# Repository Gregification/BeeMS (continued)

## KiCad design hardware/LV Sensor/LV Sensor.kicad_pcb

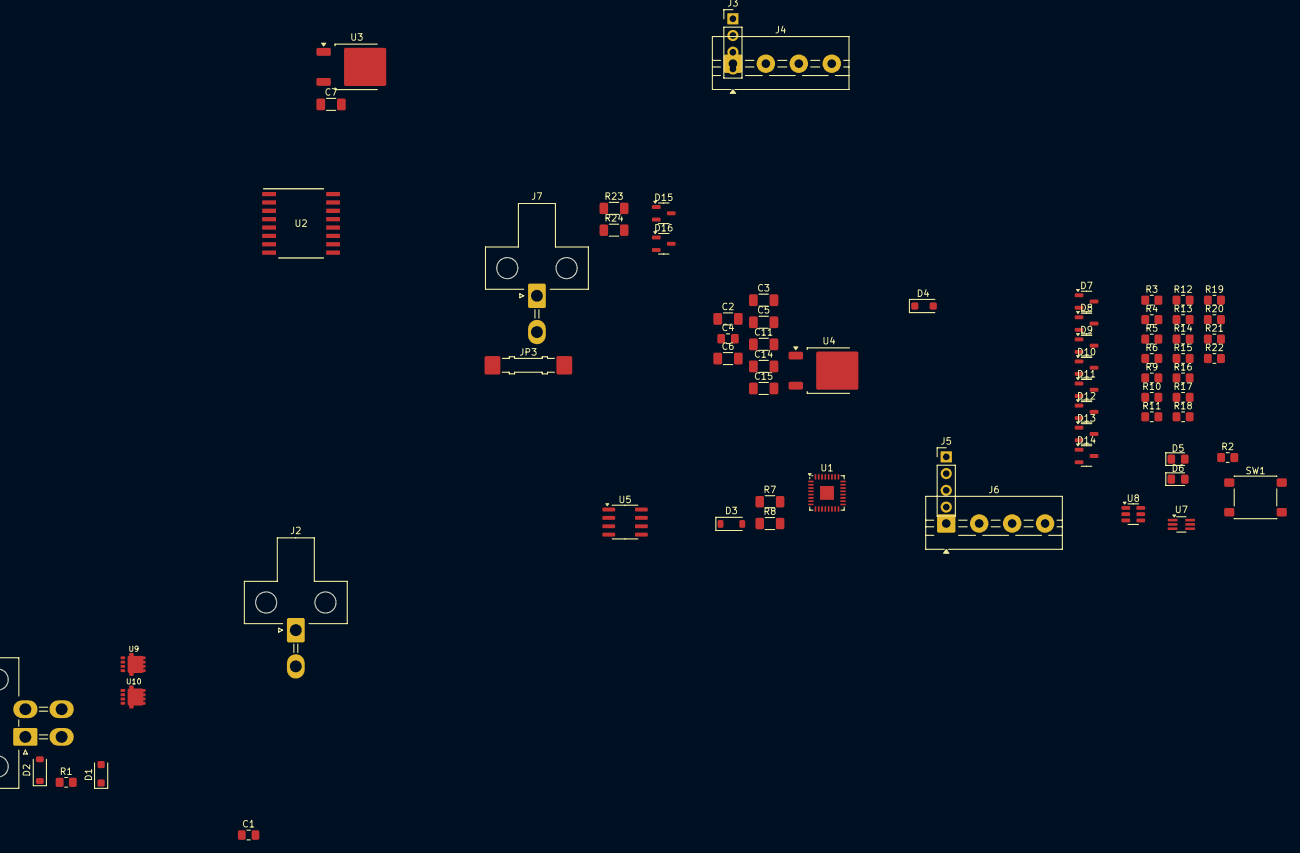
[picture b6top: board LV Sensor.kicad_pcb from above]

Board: 2 copper layers, 68 parts (0 on the bottom side), 42 nets, no tracks yet.

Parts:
C1, C4: 470n; C_0805_2012Metric_Pad1.18x1.45mm_HandSolder
C2, C6, C7, C14: 10u; C_1206_3216Metric_Pad1.33x1.80mm_HandSolder
C3, C15: 100n; C_1206_3216Metric_Pad1.33x1.80mm_HandSolder
C5, C11: 220n; C_1206_3216Metric_Pad1.33x1.80mm_HandSolder
D1, D4: 18V; D_SOD-123F
D2, D3: D_SOD-123
D5: GREEN; D_0805_2012Metric_Pad1.15x1.40mm_HandSolder
D6: RED; D_0805_2012Metric_Pad1.15x1.40mm_HandSolder
D7, D8, D9, D10, D11, D12, D13, D14, D15, D16: BAT54S; SOT-23-3
J1: Conn_01x04_Pin; Molex_Mini-Fit_Jr_5569-04A1_2x02_P4.20mm_Horizontal
J2, J7: Conn_01x02_Pin; Molex_Mini-Fit_Jr_5569-02A1_2x01_P4.20mm_Horizontal
J3, J5: TH; PinHeader_1x04_P2.54mm_Vertical
J4, J6: SCREW; TerminalBlock_MaiXu_MX126-5.0-04P_1x04_P5.00mm
JP3: Jumper_2_Open; Jumper_Harwin_S1621_P10.9mm
R1, R2: 200k; R_0805_2012Metric_Pad1.20x1.40mm_HandSolder
R3, R4: 220; R_0805_2012Metric_Pad1.20x1.40mm_HandSolder
R5, R6, R9, R10, R11, R12, R13, R14, R15, R16, R17, R18, R19, R20, R21, R22: 100k; R_0805_2012Metric_Pad1.20x1.40mm_HandSolder
R7: 49.9k; R_1206_3216Metric_Pad1.30x1.75mm_HandSolder
R8: 100k; R_1206_3216Metric_Pad1.30x1.75mm_HandSolder
R23, R24: 4.99k; R_1206_3216Metric_Pad1.30x1.75mm_HandSolder
SW1: SW_Push; SW_SPST_PTS645Sx43SMTR92
U1: MSPM0G3507 RHB32; Texas_RHB0032M_VQFN-32-1EP_5x5mm_P0.5mm_EP2.1x2.1mm
U2: ISO1042BDW; DW0016B_M
U3, U4: KA78M05_TO252; TO-252-2
U5: L78L33_SO8; SOIC-8_3.9x4.9mm_P1.27mm
U7: HBDM60V600X; SOT-363_SC-70-6_Handsoldering
U8: MCP3421A0T-ECH; SOT-23-6
U9, U10: DXTN80100CFGQ; PowerDI3333-8_SWP

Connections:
+3V3: C2.1, C14.1, C15.1, D7.2 (K), D8.2 (K), D9.2 (K), D10.2 (K), D11.2 (K), D12.2 (K), D13.2 (K), D14.2 (K), R3.2, R4.2, R7.1, R23.1, R24.2, U1.4 (VDD), U5.1 (OUT), U8.5 (V_{DD})
+BATT: D3.2 (A), J2.1
-BATT: C2.2, C3.2, C4.2, C5.2, C6.2, C11.2, C14.2, C15.2, D4.2 (A), D5.1 (K), D6.1 (K), D7.1 (A), D8.1 (A), D9.1 (A), D10.1 (A), D11.1 (A), D12.1 (A), D13.1 (A), D14.1 (A), J2.2, J7.1, JP3.2 (B), R8.1, R11.1, R12.1, R13.1, R14.1, R16.1, R18.1, R20.1, R22.1, SW1.2, U1.5 (VSS), U1.33 (CENTER_PAD), U2.2 (GND1), U2.8 (GND1), U4.2 (GND), U5.2 (GND), U5.3 (GND), U5.6 (GND), U5.7 (GND)
/ADC0_0: D11.3 (COM), R5.2, R11.2, U1.31 (PA27_A0_0_CAN_RX)
/ADC0_1: D12.3 (COM), R6.2, R12.2, U1.30 (PA26_A0_1_CAN_TX)
/ADC0_2: D13.3 (COM), R9.2, R13.2, U1.29 (PA25_A0_2)
/ADC0_3: D14.3 (COM), R10.2, R14.2, U1.28 (PA24_A0_3)
/ADC1_0: D9.3 (COM), R15.2, R16.2, U1.19 (PA15_A1_0)
/ADC1_1: D7.3 (COM), R17.2, R18.2, U1.20 (PA16_A1_1)
/ADC1_2: D8.3 (COM), R19.2, R20.2, U1.21 (PA17_A1_2)
/ADC1_3: D10.3 (COM), R21.2, R22.2, U1.22 (PA18_A1_3)
/CAN pwr +: D2.2 (A), J1.1
/CAN pwr -: C1.2, C7.2, D1.2 (A), J1.4, JP3.1 (A), U2.9 (GND2), U2.10 (GND2), U2.15 (GND2), U3.2 (GND)
/CAN_H: J1.2, U2.13 (CANH)
/CAN_L: J1.3, U2.12 (CANL)
/CAN_RX: U1.17 (PA13_CAN_RX), U2.5 (RXD)
/CAN_TX: U1.16 (PA12_CAN_TX), U2.3 (TXD)
/I2C1_SCL: R24.1, U1.8 (PA4_LFXOUT), U8.3 (SCL)
/I2C1_SDA: R23.2, U1.7 (PA3_LFXIN), U8.4 (SDA)
/RESET_N: C3.1, R7.2, SW1.1, U1.3 (RST_N)
unnamed: C1.1, D1.1 (K), R1.2, U9.1 (B)
unnamed: D2.1 (K), R1.1, U9.3 (C)
unnamed: D3.1 (K), R2.1, U10.3 (C)
unnamed: C4.1, D4.1 (K), R2.2, U10.1 (B)
unnamed: D5.2 (A), U7.4 (EQ2)
unnamed: D6.2 (A), U7.6 (CQ1)
unnamed: J3.1, J4.1, R5.1
unnamed: J3.2, J4.2, R6.1
unnamed: J3.3, J4.3, R9.1
unnamed: J3.4, J4.4, R10.1
unnamed: J5.1, J6.1, R15.1
unnamed: J5.2, J6.2, R17.1
unnamed: J5.3, J6.3, R19.1
unnamed: J5.4, J6.4, R21.1
unnamed: C6.1, J7.2, U4.3 (VO)
unnamed: R8.2, U1.6 (PA2_ROSC)
unnamed: C5.1, C11.1, U1.32 (VCORE)
unnamed: U3.1 (VI), U9.2 (E)
unnamed: C7.1, U2.11 (VCC2), U2.16 (VCC2), U3.3 (VO)
unnamed: R4.1, U7.3 (CQ2)
unnamed: R3.1, U7.5 (EQ1)
unnamed: U4.1 (VI), U5.8 (IN), U10.2 (E)

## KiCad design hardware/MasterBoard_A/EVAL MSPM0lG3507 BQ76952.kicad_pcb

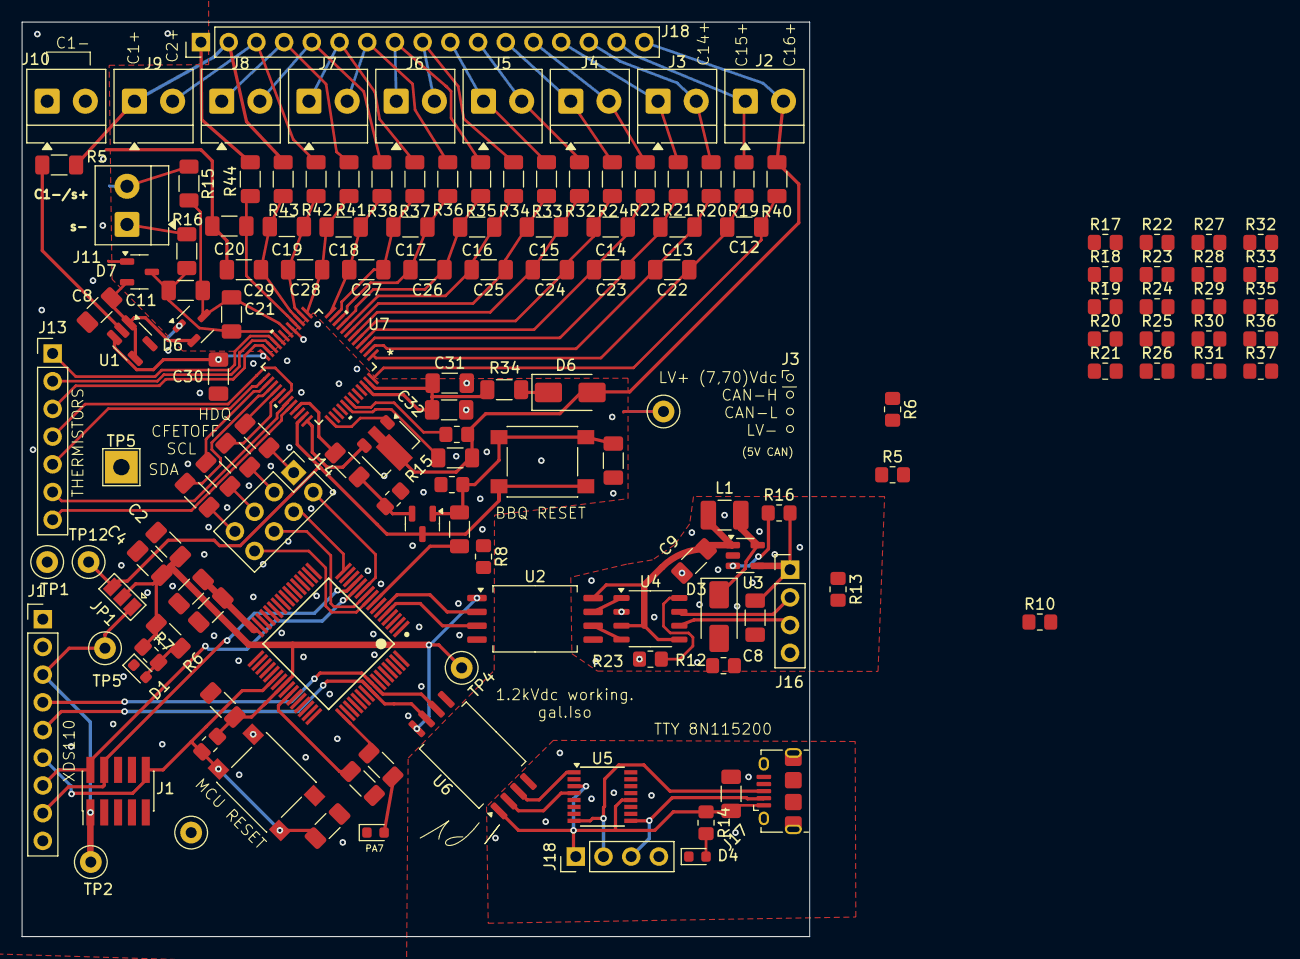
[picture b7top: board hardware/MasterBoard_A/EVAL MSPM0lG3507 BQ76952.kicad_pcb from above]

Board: 2 copper layers, 72.2 x 83.8 mm, 145 parts (0 on the bottom side), 103 nets.

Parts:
C1, C7, C11: 100n; C_1206_3216Metric_Pad1.33x1.80mm_HandSolder
C2, C3, C5, C6, C8#2, C12, C13, C14, C15, C16, C17, C18, C19, C20, C22, C23, C24, C25, C26, C27, C28, C29: 220n; C_1206_3216Metric_Pad1.33x1.80mm_HandSolder
C4, C8, C9, C10, C30, C31, C32: 10u; C_1206_3216Metric_Pad1.33x1.80mm_HandSolder
C21: 100p; C_1206_3216Metric_Pad1.33x1.80mm_HandSolder
D1, D2, D4: LED; LED_0603_1608Metric
D3, D6#2: ES1D; D_SMA
D6, D7: BAT54S; SOT-23-3
J1: Conn_02x05_Odd_Even; PinHeader_2x05_P1.27mm_Vertical_SMD
J1#2: Conn_01x09_Socket; PinHeader_1x09_P2.54mm_Vertical
J2, J3, J4, J5, J6, J7, J8, J9, J10, J11: Screw_Terminal_01x02; TerminalBlock_MetzConnect_Type059_RT06302HBWC_1x02_P3.50mm_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
J13: Conn_01x07_Pin; PinHeader_1x07_P2.54mm_Vertical
J14: Conn_02x04_Odd_Even; PinHeader_2x04_P2.54mm_Vertical
J16, J18: Conn_01x04_Socket; PinHeader_1x04_P2.54mm_Vertical
J17: USB_B_Micro; USB_Micro-B_Amphenol_10118194-0001LF_Horizontal
J18#2: Conn_01x17_Socket; PinHeader_1x17_P2.54mm_Vertical
JP1: SolderJumper_3_Open; SolderJumper-3_P1.3mm_Open_Pad1.0x1.5mm
L1: 22u; L_1210_3225Metric_Pad1.42x2.65mm_HandSolder
Q6: 2N7002; SOT-23
R1, R15, R50: 4.99k; R_1206_3216Metric_Pad1.30x1.75mm_HandSolder
R1#2, R2, R3, R4, R5, R34#2: 150; R_1206_3216Metric_Pad1.30x1.75mm_HandSolder
R2#2, R7#2, R11, R16#2, R23: 200k; R_0805_2012Metric_Pad1.20x1.40mm_HandSolder
R5#2, R7, R8, R14, R35#2, R36, R37#2: 3.32k; R_0805_2012Metric_Pad1.20x1.40mm_HandSolder
R6, R11#2: 750; R_1206_3216Metric_Pad1.30x1.75mm_HandSolder
R6#2, R10, R12, R13: 97.6k; R_0805_2012Metric_Pad1.20x1.40mm_HandSolder
R9: 10k; R_0805_2012Metric_Pad1.20x1.40mm_HandSolder
R9#2: 100k; R_1206_3216Metric_Pad1.30x1.75mm_HandSolder
R15#2, R16: 100; R_1206_3216Metric_Pad1.30x1.75mm_HandSolder
R17, R18, R19, R20#2, R21#2, R22, R23#2, R24#2, R25, R26, R27, R28, R29, R30, R31, R32, R33#2: 24.9; R_0805_2012Metric_Pad1.20x1.40mm_HandSolder
R19#2, R20, R21, R22#2, R24, R32#2, R33, R34, R35, R36#2, R37, R38, R40, R41, R42, R43, R44: 50; R_1206_3216Metric_Pad1.30x1.75mm_HandSolder
SW1, SW2: SW_Push; SW_SPST_PTS645
TP1, TP2, TP3, TP4, TP4#2, TP5, TP12: TestPoint; TestPoint_Loop_D2.50mm_Drill1.0mm_LowProfile
TP5#2: TestPoint; TestPoint_THTPad_3.0x3.0mm_Drill1.5mm
U1: MCU-MSM0G3507SPM; MSPM0G3507-64-IPC_A
U1#2: MCP6L01Rx-xOT; SOT-23-5_HandSoldering
U2, U6: STISO620; SOIC-8_7.5x5.85mm_P1.27mm
U3: RAA211805; TSOT-23-5
U4: MCP2542FDxMF; JEITA_SOIC-8_3.9x4.9mm_P1.27mm
U5: FT230XS; SSOP-16_3.9x4.9mm_P0.635mm
U7: PBQ76952PFBT; BQ76952_PFB48_TEX
U8: FCX495; SOT-89-3

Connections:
+BATT: D6#2.2 (A), J2.2, J18#2.17, R9.2, R15.1, R17.1, R40.1
-BATT: C1.1, C2.2, C3.2, C4.2, C5.2, C6.2, C7.2, C8#2.1, C20.2, C29.2, C30.2, C31.2, C32.2, D1.1 (K), D2.1 (K), D6.1 (A), D7.1 (A), J1.3, J1.5, J1.7, J1.9, J1#2.1, J10.1, J11.2, J18#2.1, R2#2.1, R6#2.1, R9#2.1, R11.1, R15#2.1, R44.2, SW2.2, TP3.1, TP4.1, TP5#2.1, U1.41 (VSS), U1#2.5 (V-), U2.1 (VDD1), U6.5 (GND2), U7.17 (VSS)
/BQ76952 16C/1N: J10.2, R33#2.1
/BQ76952 16C/1P: J9.1, J18#2.2, R5.2, R32.1, R43.1
/BQ76952 16C/2P: J9.2, J18#2.3, R31.1, R42.1
/BQ76952 16C/3P: J8.1, J18#2.4, R30.1, R41.1
/BQ76952 16C/4P: J8.2, J18#2.5, R29.1, R38.1
/BQ76952 16C/5P: J7.1, J18#2.6, R28.1, R37.1
/BQ76952 16C/6P: J7.2, J18#2.7, R27.1, R36#2.1
/BQ76952 16C/7P: J6.1, J18#2.8, R26.1, R35.1
/BQ76952 16C/8P: J6.2, J18#2.9, R25.1, R34.1
/BQ76952 16C/9P: J5.1, J18#2.10, R24#2.1, R33.1
/BQ76952 16C/10P: J5.2, J18#2.11, R23#2.1, R32#2.1
/BQ76952 16C/11P: J4.1, J18#2.12, R22.1, R24.1
/BQ76952 16C/12P: J4.2, J18#2.13, R21#2.1, R22#2.1
/BQ76952 16C/13P: J3.1, J18#2.14, R20#2.1, R21.1
/BQ76952 16C/14P: J3.2, J18#2.15, R19.1, R20.1
/BQ76952 16C/15P: J2.1, J18#2.16, R18.1, R19#2.1
/BQ76952 16C/ALERT: J13.5, U7.25 (ALERT)
/BQ76952 16C/BAT: C31.1, C32.1, R34#2.2, R36.2, R37#2.2, U7.46 (CP1), U7.47 (BAT), U8.2
/BQ76952 16C/CFETOFF: R1#2.1, U7.29 (CFETOFF)
/BQ76952 16C/DCHG: J13.6, U7.31 (DCHG)
/BQ76952 16C/DDSG: J13.7, U7.32 (DDSG)
/BQ76952 16C/DFETOFF: J13.4, U7.30 (DFETOFF)
/BQ76952 16C/HDQ: R3.1, U7.28 (HDQ)
/BQ76952 16C/PACK-: J11.1, R16.1
/BQ76952 16C/RST_SHUT: R5#2.1, R50.1, U7.33 (RST_SHUT)
/BQ76952 16C/SCL: R2.2, U7.26 (SCL)
/BQ76952 16C/SDA: R4.2, U7.27 (SDA)
/BQ76952 16C/TS1: J13.1, U7.21 (TS1)
/BQ76952 16C/TS2: J13.2, U7.22 (TS2)
/BQ76952 16C/TS3: J13.3, U7.23 (TS3)
/GLV interface/5v: C9.1, L1.2, U2.5 (GND2), U3.1 (VOUT), U4.3 (VDD), U4.5 (VIO)
/GLV interface/CAN_H: J16.3, U4.7 (CANH)
/GLV interface/CAN_L: J16.4, U4.6 (CANL)
/GLV interface/GLV+: C8.1, J16.2, R13.2, R16#2.2, U3.4 (VIN)
/GLV interface/GLV-: C8.2, C9.2, D3.2 (A), J16.1, R12.1, R23.1, U2.8 (VDD2), U3.2 (GND), U4.2 (VSS)
/UART_USB/5V: C10.1, J17.1 (VBUS), J18.1, R14.1, U5.3 (VCCIO), U5.12 (VCC), U6.1 (VDD1)
/UART_USB/GND: C10.2, D4.1 (K), J17.5 (GND), J18.4, U5.5 (GND), U5.13 (GND), U6.4 (GND1)
/XDS_3v_supply: J1.1, J1#2.3, JP1.1 (A), TP2.1, TP5.1
unnamed: C1.2, R5#2.2, R6#2.2, R8.1, SW1.2
unnamed: D1.2 (A), R6.1, R7.2
unnamed: D2.2 (A), R11#2.2
unnamed: D3.1 (K), L1.1, U3.5 (SW)
unnamed: D4.2 (A), R14.2
unnamed: C8#2.2, D6.2 (K), D6#2.1 (K), D7.2 (K), R34#2.1, U1#2.1, U1#2.4 (-)
unnamed: J14.1, R3.2
unnamed: J14.3, R1#2.2
unnamed: J14.5, R2.1
unnamed: J14.7, R4.1
unnamed: J17.3 (D+), J18.2, U5.8 (USBDP)
unnamed: J17.2 (D-), J18.3, U5.9 (USBDM)
unnamed: Q6.1 (G), R1.1, R11.2
unnamed: Q6.2 (S), R2#2.2, R50.2
unnamed: R35#2.2, R37#2.1
unnamed: R9#2.2, U1.42 (PA2_ROSC)
unnamed: R5.1, U1#2.2 (V+)
unnamed: C5.1, C6.1, U1.32 (VCORE)
unnamed: U2.6 (RXA), U4.1 (TXD)
unnamed: U2.7 (TXB), U4.4 (RXD)
unnamed: R13.1, U3.3 (EN)
unnamed: R12.2, U4.8 (STBY)
unnamed: U5.4 (RXD), U6.2 (RXB)
unnamed: U5.1 (TXD), U6.3 (TXA)
unnamed: U7.37 (BREG), U8.1
unnamed: R36.1, U7.41 (LD)
unnamed: R35#2.1, U7.42 (PACK)
unnamed: C30.1, U7.24 (REG18)
unnamed: U7.36 (REGIN), U8.3
unnamed: C11.2, C21.2, R16.2, U7.20 (SRN)
unnamed: C11.1, C21.1, R15#2.2, U7.18 (SRP)
unnamed: C20.1, R33#2.2, U7.16 (VC0)
unnamed: C19.2, C29.1, R32.2, U7.15 (VC1)
unnamed: C19.1, C28.2, R31.2, U7.14 (VC2)
unnamed: C18.2, C28.1, R30.2, U7.13 (VC3)
unnamed: C18.1, C27.2, R29.2, U7.12 (VC4)
unnamed: C17.2, C27.1, R28.2, U7.11 (VC5)
unnamed: C17.1, C26.2, R27.2, U7.10 (VC6)
unnamed: C16.2, C26.1, R26.2, U7.9 (VC7)
unnamed: C16.1, C25.2, R25.2, U7.8 (VC8)
unnamed: C15.2, C25.1, R24#2.2, U7.7 (VC9)
unnamed: C15.1, C24.2, R23#2.2, U7.6 (VC10)
unnamed: C14.2, C24.1, R22.2, U7.5 (VC11)
unnamed: C14.1, C23.2, R21#2.2, U7.4 (VC12)
unnamed: C13.2, C23.1, R20#2.2, U7.3 (VC13)
unnamed: C13.1, C22.2, R19.2, U7.2 (VC14)
unnamed: C12.2, C22.1, R18.2, U7.1 (VC15)
unnamed: C12.1, R17.2, U7.48 (VC16)
PA7: R11#2.1, U1.49 (PA7)
PA10_UART0-TX_XDS: J1#2.5, U1.56 (PA10), U6.7 (TXB)
PA11_UART0-RX_XDS: J1#2.4, U1.57 (PA11), U6.6 (RXA)
PA12_CAN_TX: U1.5 (PA12_CAN_TX), U2.3 (TXA)
PA13_CAN_RX: U1.6 (PA13_CAN_RX), U2.2 (RXB)
PA15_BBQ_RESET: R1.2, R8.2, U1.8 (PA15_A1_0)
PA16_SPI1_MISO: J14.8, U1.9 (PA16_A1_1)
PA17_SPI1_SCK: J14.6, U1.10 (PA17_A1_2)
PA18_SPI1_MOSI: J14.2, U1.11 (PA18_A1_3)
PA19_SWDIO: J1.2, J1#2.7, U1.12 (PA19_SWDIO)
PA20_SWCLK: J1.4, J1#2.8, U1.13 (PA20_SWCLK)
PB19_BBQ_CS: J14.4, U1.16 (PB19_A1_6)
RST_N: C7.1, J1.10, J1#2.6, R7#2.1, R10.1, SW2.1, U1.38 (RST_N)
VDD: C2.1, C3.1, C4.1, JP1.2 (C), R6.2, R7.1, R7#2.2, R10.2, TP4#2.1, U1.40 (VDD), U2.4 (GND1), U6.8 (VDD2)
onboard 3.3v src: JP1.3 (B), Q6.3 (D), SW1.1, TP1.1, TP12.1, U7.35 (REG1)
